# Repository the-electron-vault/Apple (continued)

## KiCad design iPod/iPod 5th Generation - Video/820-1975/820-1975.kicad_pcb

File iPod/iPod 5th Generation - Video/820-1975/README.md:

# 820-1975 - iPod Video Main Board

## Overview
This is an open-source, KiCad-based 820-1975 PCBA that has been reverse-engineered from a physical board.

## Disclaimer
The information contained in this repository has been generated via reverse-engineering of publicly available material, and is provided without warranty or guarantee of accuracy. [The Electron Vault](https://www.theelectronvault.com/) is not responsible for any losses or damages caused to equipment as a consequence of the information contained in this repository or associated documents.

## Setup
### Database Library
This project uses a local database library for all components. As the library is linked to the project through relative pathing, it should just work once the ODBC driver is installed.
1) Install an ODBC driver. I use this one http://www.ch-werner.de/sqliteodbc/
2) [Optional] Install an SQLite database editor. I use SQLiteStudio https://sqlitestudio.pl

### Theme
This KiCad project has a number of thematic customisations. These are however completely optional and everything *should* work fine with the default theme. If you however wish to install the theme, here is the procedure:
1) Install KiCad as normal.
2) Copy PREF/color/Black and White.json from the repo into the corresponding folder in your KiCad preferences.
3) Launch KiCad and open Preferences -> Colors.
4) The Black and White theme should now be available in Schematic Editor -> Colors and PCB Editor -> Colors.
5) Schematic font: Arial

## Known Limitations
As this is a reverse-engineered design, there are several limitations potentially affecting accuracy that must be acknowledged:
- **This board is not ready for production.** The intent was to make it visually accurate enough to assist with troubleshooting and repair. OpenBoardView (Landrex-BRD) compatible files (generated using [kicad-boardview](https://github.com/whitequark/kicad-boardview) exporter) are provided in the repo along with PDF schematics.
	- BoardView does not respect alphanumeric pin designation of packages like BGA/CSPs, and converts them to numeric only (nets are still correctly assigned). This is a known limitation of the kicad-boardview exporter. Either use the KiCad PCB file or net names to correlate pads with schematic.
	- Component placement is only photographically accurate - there may be mechanical interferences.
	- Board outline is best-effort. Use at your own risk.
	- Board stackup has not been recovered from the board, though the overall thickness should be representative. It's likely 6 layer. At the very least, there are blind vias on the top and bottom two layers, and potentially buried vias as well.
	- Only surface routing exists, primarily as a checklist aid/sanity check that nets have been assigned to the correct components. 
	- Trace widths are purely photographically scaled. Hand in hand with the lack of stackup definition, this also means none of it has been impedance controlled. Nevertheless minimum trace width appears to be 3 mil, so even if it were completed, you won't be able to send this through any old budget Chinese fab.
- Passive component (resistors, capacitors, inductors) values were measured with an LCR meter and rounded to the nearest standard value. Accuracy is not guaranteed.
- Ferrite beads/chip inductors are difficult to resolve as they look the same to a basic LCR and don't have physically unique features. A network analyser could be used to glean further information about frequency vs. impedance, however it still would not lead to a specific part number. Thus, for such parts (mainly found on dock connector signals and in front of switching regulators), educated substitutions have been made based on part size and expected maximum current on the line. Take the provided part numbers with a pinch of salt.
- The two 10uH wire-wound inductors found either side of the dock connector were not able to be identified, but are presumed to be Sumida brand due to stylistic similarity.
- The battery connector was not able to be confirmed, but is known to be manufactured by DDK due to the logo being embossed on the locking slider. Best guess based on an [EOL notice](https://www.ddknet.co.jp/English/order_stop_eng/list.html) on their website is that it is the FF15A series.
- The dock connector although a custom part, is clearly a Foxlink clone of the [JAE DD1 Series](https://www.jae.com/en/connectors/series/detail/id=64352). It has consequently been simply copied verbatim in this design.
- The BCM2722 (VPU) pinout is based off the sibling BCM2702 part. Thus, there may be incongruities.
- The PP5021C (MPU) pinout was assembled best-effort based on the PP5020 and PP5022 used in devices from other manufacturers. Thus, it likely has errors. Some pins such as those assigned to keyboard matrix or FireWire functions are entirely undesignated, since they're used as GPIOs in this design, and thus it's not possible to guess their specific functions based on context. The JTAG pin group has been identified, but the specific functions could not be assigned. It should not be difficult to resolve these with trial and error and an appropriate programmer.
- The pinout of the PCF50607 (PMU) is provided without guarantee. It has been speculatively assembled using context from surrounding circuits and sibling parts - PCF50605/6 and PCF50633.
- All net labels are named based on context, and thus their accuracy is not guaranteed.
- There are a handful of circuits (primarily involving FETs/BJTs) whose function was speculative or unable to be ascertained, though they are still captured faithfully in the schematic and accompanied with a note.
- The Click Wheel was reverse-engineered separately [here](https://theelectronvault.substack.com/p/ipod-video-5th-generation-click-wheel). Pin 7's function is entirely unknown currently, and there is some speculation around SDI (8) and SDO (11).
- Functions for pin 1 and 32 of the LCD connector (J2) are speculative. They go to I/O pins on the BCM2722, but are grounded on the LCD flex. Presumed therefore to be some sort of detect/interlock signal.

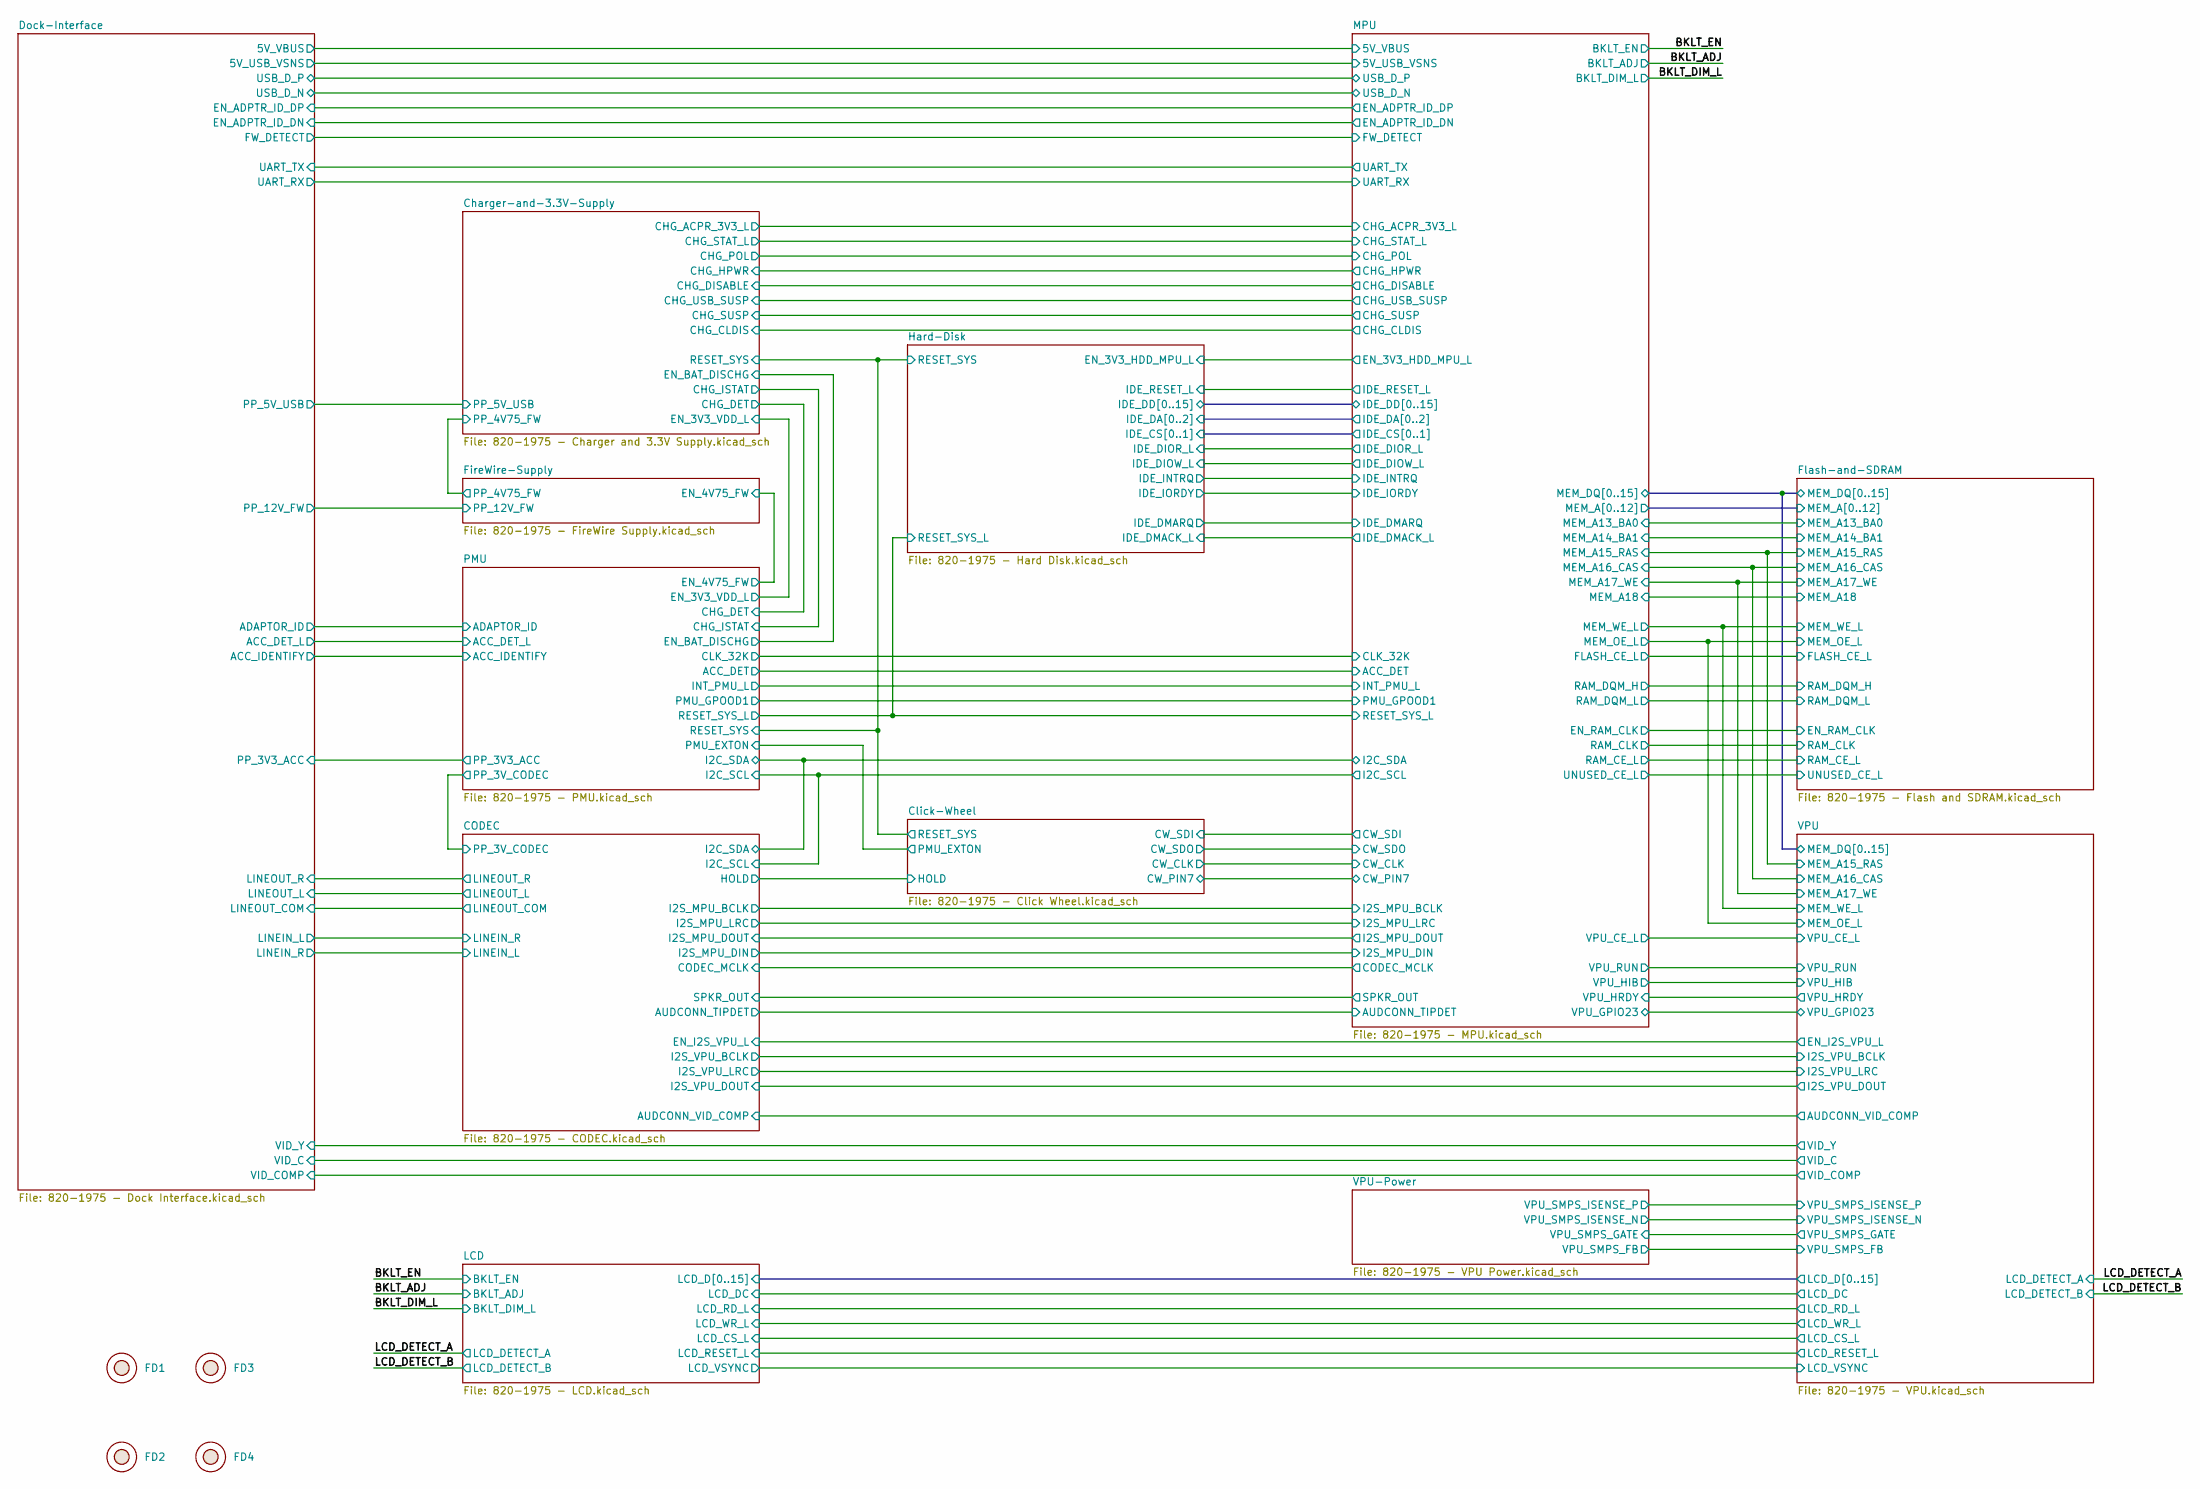
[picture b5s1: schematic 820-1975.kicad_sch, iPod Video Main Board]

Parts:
FD1, FD2, FD3, FD4: FD; FIDUCIAL

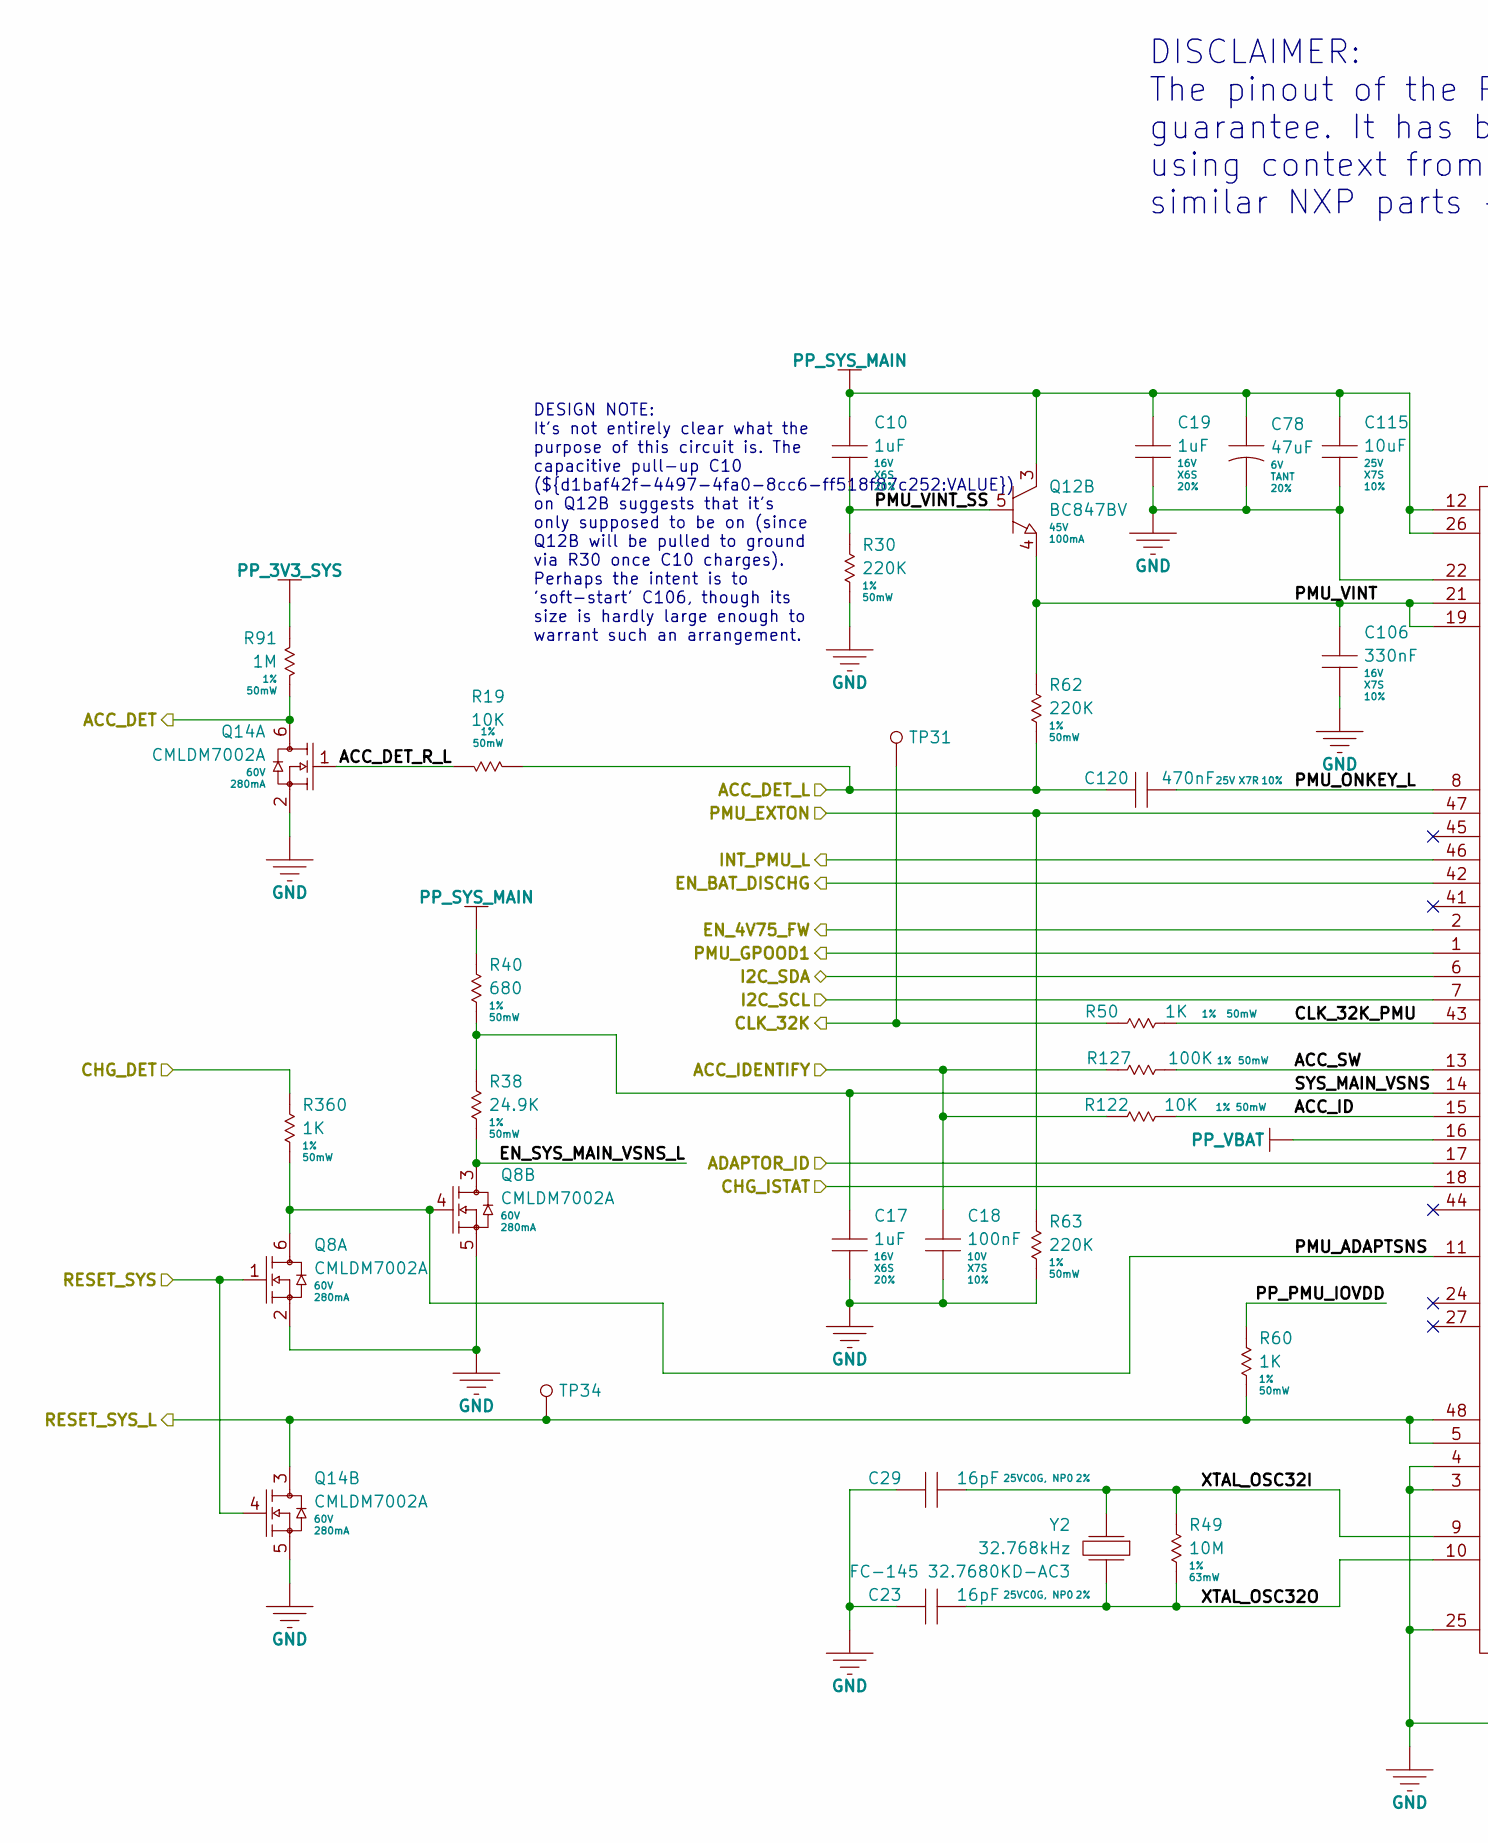
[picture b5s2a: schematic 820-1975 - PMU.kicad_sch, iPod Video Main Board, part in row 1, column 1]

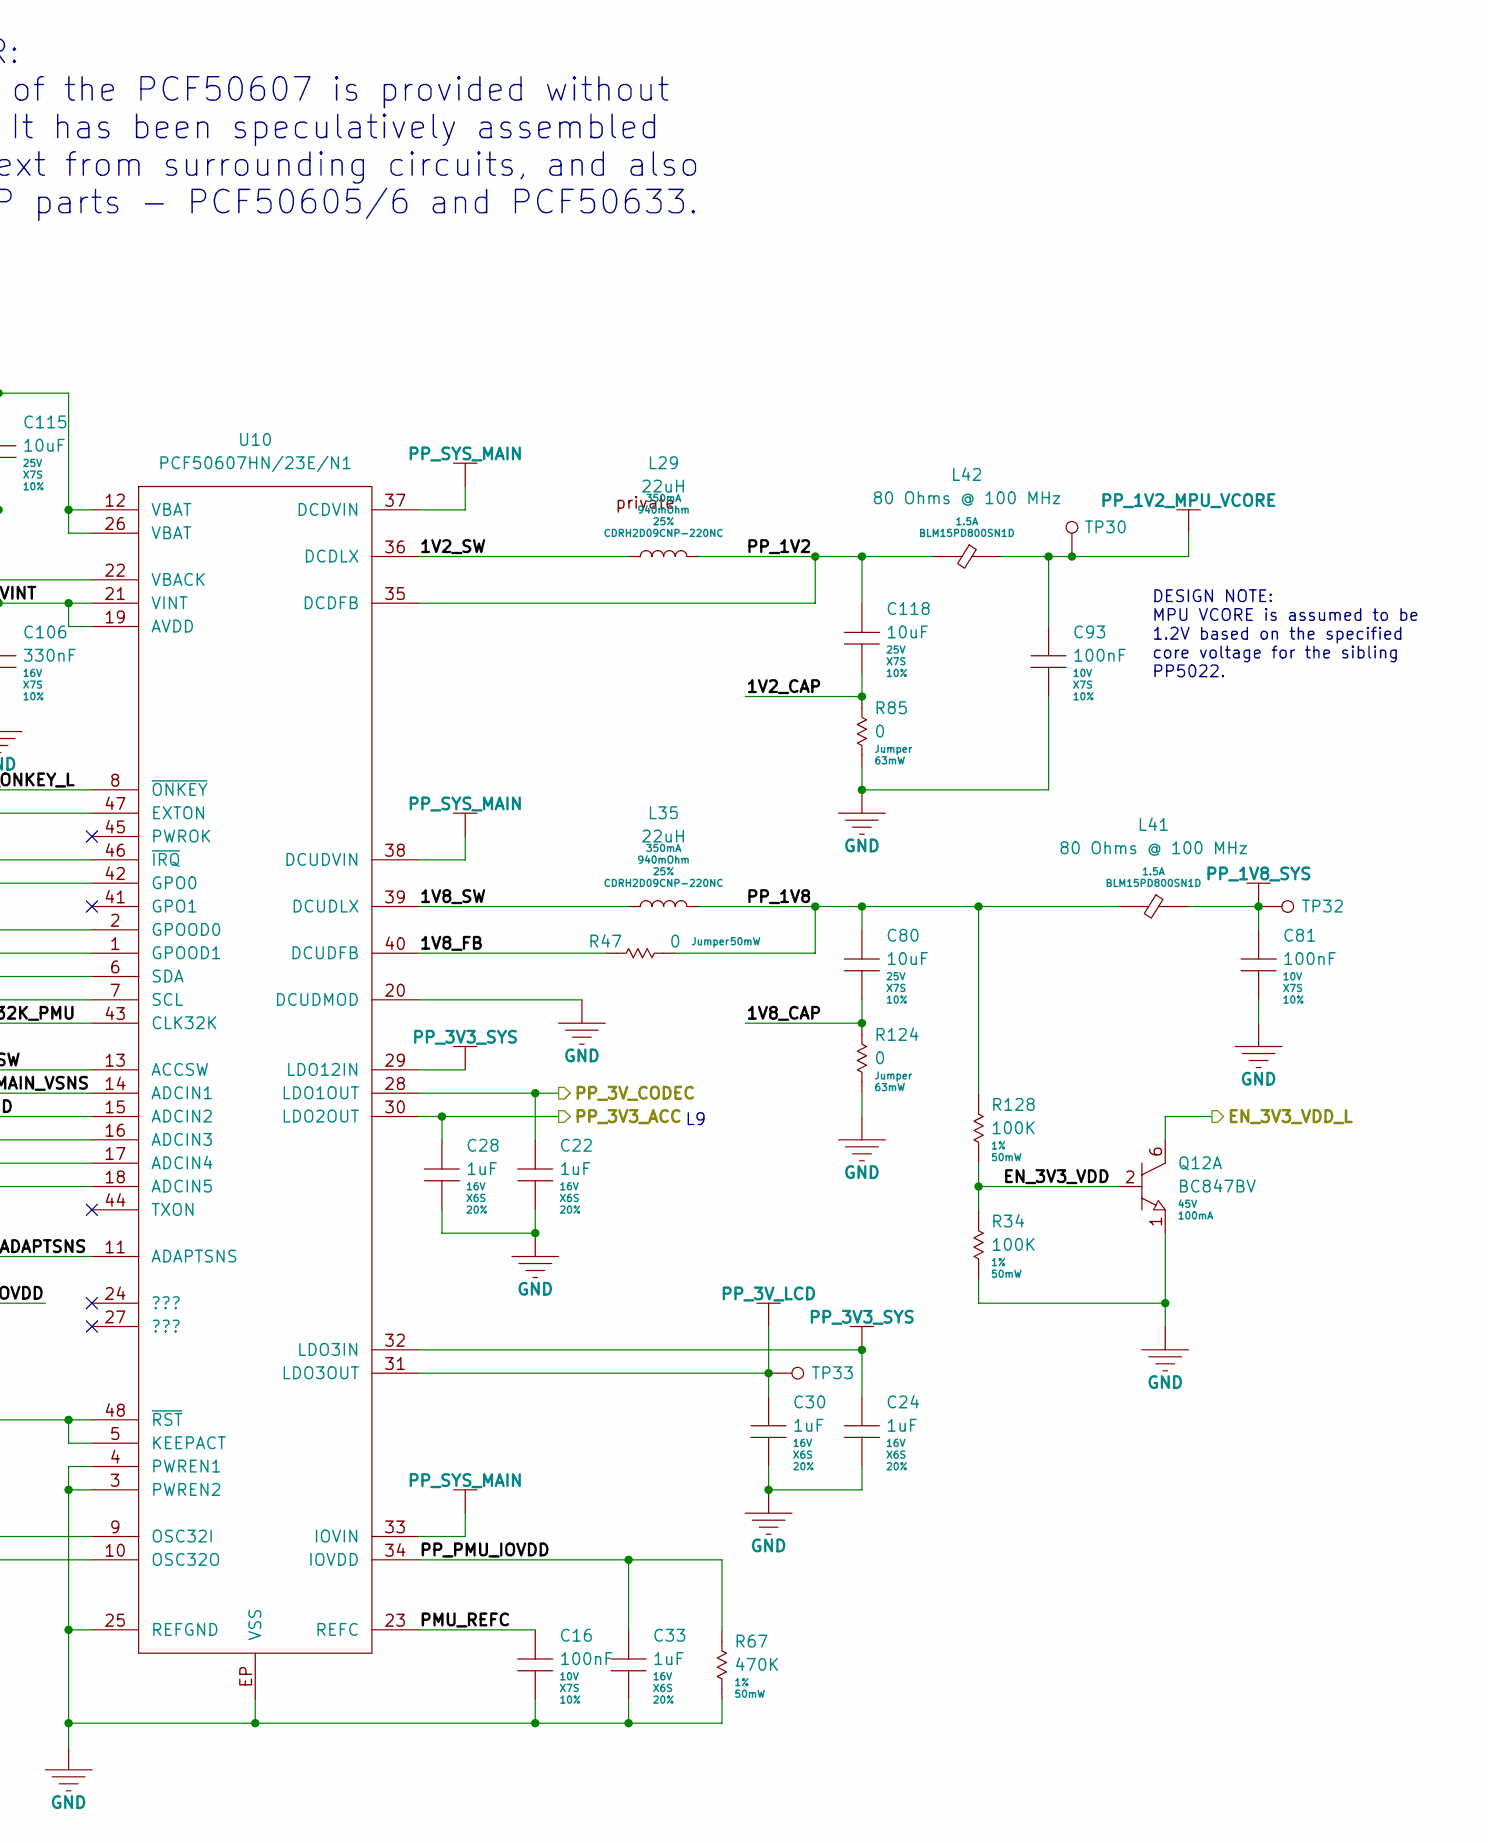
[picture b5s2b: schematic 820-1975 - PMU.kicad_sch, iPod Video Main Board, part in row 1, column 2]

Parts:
C10, C17, C19, C22, C24, C28, C30, C33: 1uF; MLCC-0402; Voltage 16V; Tolerance 20%; Manufacturer Part Number GRM155C81C105ME11J
C16, C18, C81, C93: 100nF; MLCC-0201; Voltage 10V; Tolerance 10%; Manufacturer Part Number GRM033C71A104KE14D
C23, C29: 16pF; MLCC-0201; Voltage 25V; Tolerance 2%; Manufacturer Part Number GRM0335C1E160GA01D
C78: 47uF; KEMET-T490T; Voltage 6V; Tolerance 20%; Manufacturer Part Number T490T476M006ATE800
C80, C115, C118: 10uF; MLCC-0805; Voltage 25V; Tolerance 10%; Manufacturer Part Number GRM21BC71E106KE11L
C106: 330nF; MLCC-0402; Voltage 16V; Tolerance 10%; Manufacturer Part Number CGA2B1X7S1C334K050BC
C120: 470nF; MLCC-0603; Voltage 25V; Tolerance 10%; Manufacturer Part Number GRM188R71E474KA12D
L29, L35: 22uH; CDRH2D09C; Tolerance 25%; Manufacturer Part Number CDRH2D09CNP-220NC
L41, L42: 80 Ohms @ 100 MHz; FB-0402; Manufacturer Part Number BLM15PD800SN1D
Q8, Q14: CMLDM7002A; SOT563; Voltage 60V; Manufacturer Part Number CMLDM7002A
Q12: BC847BV; SOT563; Voltage 45V; Manufacturer Part Number BC847BV
R19, R122: 10K; RES-0201; Tolerance 1%; Manufacturer Part Number CRCW020110K0FNED
R30, R62, R63: 220K; RES-0201; Tolerance 1%; Manufacturer Part Number CRCW0201220KFNED
R34, R127, R128: 100K; RES-0201; Tolerance 1%; Manufacturer Part Number CRCW0201100KFNED
R38: 24.9K; RES-0201; Tolerance 1%; Manufacturer Part Number CRCW020124K9FNED
R40: 680; RES-0201; Tolerance 1%; Manufacturer Part Number CRCW0201680RFKED
R47: 0; RES-0201; Tolerance Jumper; Manufacturer Part Number CRCW02010000Z0ED
R49: 10M; RES-0402; Tolerance 1%; Manufacturer Part Number CRCW040210M0FKEDC
R50, R60, R360: 1K; RES-0201; Tolerance 1%; Manufacturer Part Number CRCW02011K00FNED
R67: 470K; RES-0201; Tolerance 1%; Manufacturer Part Number CRCW0201470KFNED
R85, R124: 0; RES-0402; Tolerance Jumper; Manufacturer Part Number CRCW04020000Z0ED
R91: 1M; RES-0201; Tolerance 1%; Manufacturer Part Number CRCW02011M00FNED
TP30, TP31, TP32, TP33, TP34: TP; TP-SMT
U10: PCF50607HN/23E/N1; VQFN-48-0.4; Manufacturer Part Number PCF50607HN/23E/N1
Y2: 32.768kHz; FC-145; Tolerance 30ppm; Manufacturer Part Number FC-145 32.7680KD-AC3

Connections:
/CODEC/I2C_SCL: U10.7 (SCL); also elsewhere on the board
/CODEC/I2C_SDA: U10.6 (SDA); also elsewhere on the board
/CODEC/PP_3V_CODEC: C22.1, U10.28 (LDO1OUT); also elsewhere on the board
/Charger-and-3.3V-Supply/CHG_DET: R360.1; also elsewhere on the board
/Charger-and-3.3V-Supply/CHG_ISTAT: U10.18 (ADCIN5); also elsewhere on the board
/Charger-and-3.3V-Supply/EN_3V3_VDD_L: Q12.6 (C1); also elsewhere on the board
/Charger-and-3.3V-Supply/EN_BAT_DISCHG: U10.42 (GPO0); also elsewhere on the board
/Charger-and-3.3V-Supply/RESET_SYS: Q8.1 (G1), Q14.4 (G2); also elsewhere on the board
/Click-Wheel/PMU_EXTON: R63.1, U10.47 (EXTON); also elsewhere on the board
/Dock-Interface/ACC_DET_L: C120.1, R19.1, R62.2; also elsewhere on the board
/Dock-Interface/ACC_IDENTIFY: C18.1, R122.1, R127.2; also elsewhere on the board
/Dock-Interface/ADAPTOR_ID: U10.17 (ADCIN4); also elsewhere on the board
/Dock-Interface/PP_3V3_ACC: C28.1, U10.30 (LDO2OUT); also elsewhere on the board
/FireWire-Supply/EN_4V75_FW: U10.2 (GPOOD0); also elsewhere on the board
/Hard-Disk/RESET_SYS_L: Q14.3 (D2), R60.2, TP34.1, U10.5 (KEEPACT), U10.48 (~RST); also elsewhere on the board
/MPU/ACC_DET: Q14.6 (D1), R91.2; also elsewhere on the board
/MPU/CLK_32K: R50.1, TP31.1; also elsewhere on the board
/MPU/INT_PMU_L: U10.46 (~IRQ); also elsewhere on the board
/MPU/PMU_GPOOD1: U10.1 (GPOOD1); also elsewhere on the board
/PMU/1V2_CAP: C118.2, R85.1
/PMU/1V2_SW: L29.1, U10.36 (DCDLX)
/PMU/1V8_CAP: C80.2, R124.1
/PMU/1V8_FB: R47.1, U10.40 (DCUDFB)
/PMU/1V8_SW: L35.1, U10.39 (DCUDLX)
/PMU/ACC_DET_R_L: Q14.1 (G1), R19.2
/PMU/ACC_ID: R122.2, U10.15 (ADCIN2)
/PMU/ACC_SW: R127.1, U10.13 (ACCSW)
/PMU/CLK_32K_PMU: R50.2, U10.43 (CLK32K)
/PMU/EN_3V3_VDD: Q12.2 (B1), R34.1, R128.2
/PMU/EN_SYS_MAIN_VSNS_L: Q8.3 (D2), R38.2
/PMU/PMU_ADAPTSNS: Q8.4 (G2), Q8.6 (D1), R360.2, U10.11 (ADAPTSNS)
/PMU/PMU_ONKEY_L: C120.2, U10.8 (~ONKEY)
/PMU/PMU_REFC: C16.1, U10.23 (REFC)
/PMU/PMU_VINT: C106.1, Q12.4 (E2), R62.1, U10.19 (AVDD), U10.21 (VINT)
/PMU/PMU_VINT_SS: C10.2, Q12.5 (B2), R30.1
/PMU/PP_1V2: C118.1, L29.2, L42.1, U10.35 (DCDFB)
/PMU/PP_1V8: C80.1, L35.2, L41.1, R47.2, R128.1
/PMU/PP_PMU_IOVDD: C33.1, R60.1, R67.1, U10.34 (IOVDD)
/PMU/SYS_MAIN_VSNS: C17.1, R38.1, R40.2, U10.14 (ADCIN1)
/PMU/XTAL_OSC32I: C29.1, R49.1, U10.9 (OSC32I), Y2.1
/PMU/XTAL_OSC32O: C23.1, R49.2, U10.10 (OSC32O), Y2.2
GND: C16.2, C17.2, C18.2, C19.2, C22.2, C23.2, C24.2, C28.2, C29.2, C30.2, C33.2, C78.2, C81.2, C93.2, C106.2, C115.2, Q8.2 (S1), Q8.5 (S2), Q12.1 (E1), Q14.2 (S1), Q14.5 (S2), R30.2, R34.2, R63.2, R67.2, R85.2, R124.2, U10.3 (PWREN2), U10.4 (PWREN1), U10.20 (DCUDMOD), U10.22 (VBACK), U10.25 (REFGND), U10.EP (VSS); also elsewhere on the board
PP_1V2_MPU_VCORE: C93.1, L42.2, TP30.1; also elsewhere on the board
PP_1V8_SYS: C81.1, L41.2, TP32.1; also elsewhere on the board
PP_3V3_SYS: C24.1, R91.1, U10.29 (LDO12IN), U10.32 (LDO3IN); also elsewhere on the board
PP_3V_LCD: C30.1, TP33.1, U10.31 (LDO3OUT); also elsewhere on the board
PP_SYS_MAIN: C10.1, C19.1, C78.1, C115.1, Q12.3 (C2), R40.1, U10.12 (VBAT), U10.26 (VBAT), U10.33 (IOVIN), U10.37 (DCDVIN), U10.38 (DCUDVIN); also elsewhere on the board
PP_VBAT: U10.16 (ADCIN3); also elsewhere on the board

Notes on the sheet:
DESIGN NOTE: MPU VCORE is assumed to be 1.2V based on the specified core voltage for the sibling PP5022.
DISCLAIMER: The pinout of the PCF50607 is provided without guarantee. It has been speculatively assembled using context from surrounding circuits, and also similar NXP parts - PCF50605/6 and PCF50633.
DESIGN NOTE: It's not entirely clear what the purpose of this circuit is. The capacitive pull-up C10 (${d1baf42f-4497-4fa0-8cc6-ff518f87c252:VALUE}) on Q12B suggests that it's only supposed to be on (since Q12B will be pulled to ground via R30 once C10 charges). Perhaps the intent is to 'soft-start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
